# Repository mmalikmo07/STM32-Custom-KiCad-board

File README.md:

# STM32F103 Development Board

A 2-layer, 45 × 40 mm development board built around the STM32F103C8T6 (Arm Cortex-M3, 72 MHz), designed in KiCad 9 from schematic through layout to Gerbers. It's powered and programmed over USB, with SWD for debugging and breakout headers for UART and I²C.

This was my first full board. It began as a guided KiCad tutorial build, which is why the files are named `KiCad-STM32-tut`. Below are the design choices and what I'd change in the next revision.

## Status

**Design complete, not yet fabricated.** The fab-ready Gerbers and drill files are in [`gerbers/`](gerbers/). The next steps are fabrication, assembly and bring-up (see below).

## Block overview

| Block | Implementation | Notes |
|---|---|---|
| MCU | STM32F103C8T6, LQFP-48 | 64 KB flash, 20 KB SRAM |
| Power | USB VBUS (5 V) → AMS1117-3.3 LDO (SOT-223) | 22 µF bulk capacitors on the input and output, as the AMS1117 needs for stability |
| Decoupling | 100 nF on the VDD pins, plus 10 µF bulk on 3.3 V | |
| Analogue supply | VDDA fed from 3.3 V through a 120 Ω ferrite bead, with 1 µF + 10 nF | Keeps digital switching noise off the ADC reference |
| Clock | 16 MHz crystal (3.2 × 2.5 mm), 10 pF load caps | The PLL gives 72 MHz SYSCLK, and the 48 MHz USB clock is derived from it |
| USB | Micro-B (Würth 629105150521), USB FS on PA11/PA12 | 1.5 kΩ pull-up on D+, which the F103 needs because it has no internal one |
| Boot | SPDT slide switch → 10 kΩ → BOOT0 | Selects the system bootloader or flash at reset |
| Debug / IO | 4-pin headers: SWD (SWDIO, SWCLK), USART1 (remapped to PB6/PB7), I²C2 (PB10/PB11, 1.5 kΩ pull-ups) | |
| Indicator | Power LED (0603) | |
| Mechanical | 4 × M2 mounting holes | |

**Layout:** 2 layers, with a solid GND pour on the bottom layer as the return plane. The top layer carries GND, 3.3 V and VBUS pours around the signal routing. Passives are mostly 0402.

## Rev B: what I'd change

These are the issues I found reviewing my own netlist:

1. **USB connector shield is floating.** The shield pads are unconnected. Tying them to GND through a ferrite bead or an RC network (e.g. 1 MΩ ∥ 4.7 nF) would improve EMI and ESD behaviour.
2. **No ESD protection on the USB lines.** Add a TVS array such as the USBLC6-2SC6 on D+/D− and VBUS.
3. **No input protection.** Add a polyfuse on VBUS and reverse-current protection if the board will ever be powered from the headers.
4. **Regulator choice.** An LDO is fine at this board's load. At around 100 mA it dissipates (5 − 3.3) × 0.1 ≈ 0.17 W. If I add peripherals that draw hundreds of mA, I'd move to a buck converter for efficiency.
5. **Connector.** USB-C with 5.1 kΩ CC pull-downs would make it work with modern cables and chargers.

## Bring-up plan

1. Visual inspection, then check continuity and look for shorts between 3.3 V, VBUS and GND
2. Power from a current-limited bench supply and check the 3.3 V rail and its ripple
3. Connect over SWD with an ST-Link and read the device ID
4. Flash a blinky over SWD, then test USB DFU through the BOOT0 switch
5. Check the 16 MHz HSE on a scope, then confirm the PLL by toggling a GPIO with MCO

## Files

```
KiCad-STM32-tut.kicad_pro / .kicad_sch / .kicad_pcb   KiCad 9 project
gerbers/                                             Gerbers, drill files, and a zipped fab package
3d-models/                                           STEP model for the USB connector
```

Tools: KiCad 9, STM32CubeMX (pin planning).

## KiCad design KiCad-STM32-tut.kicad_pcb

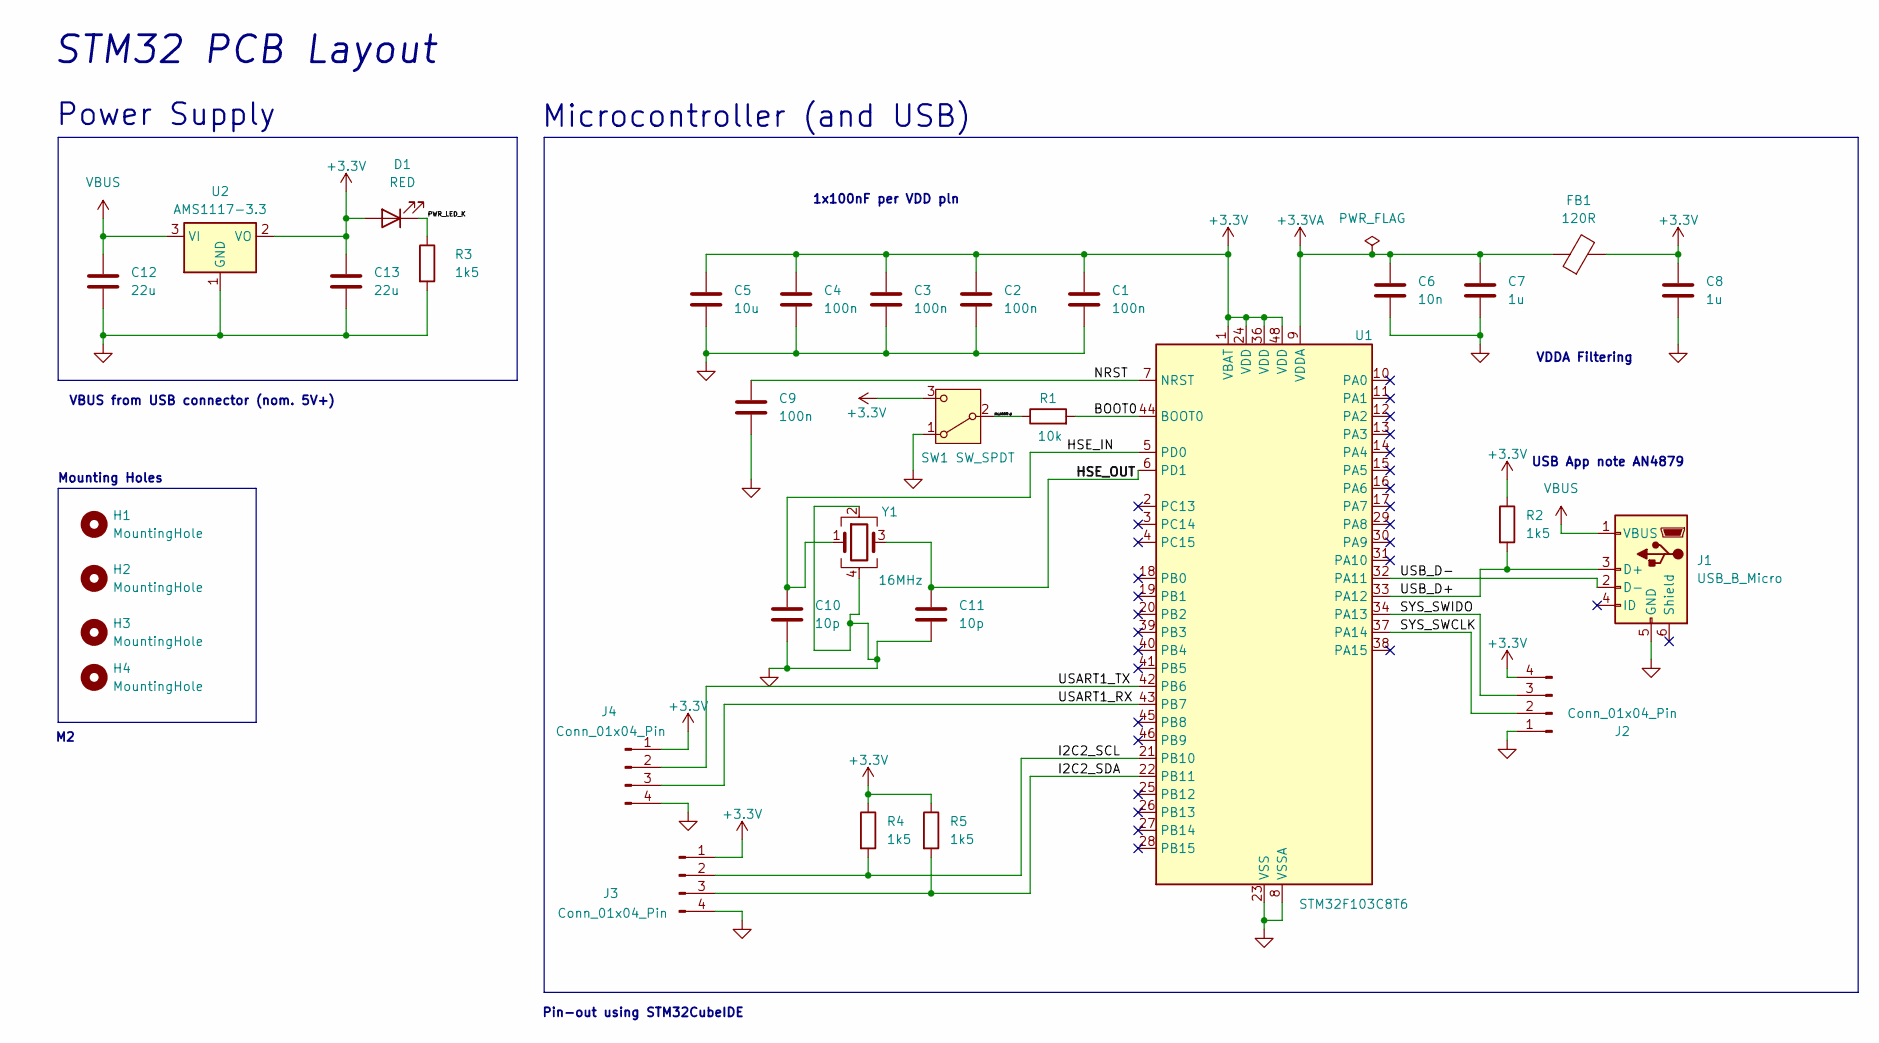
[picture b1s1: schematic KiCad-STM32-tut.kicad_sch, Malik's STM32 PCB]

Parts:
C1, C2, C3, C4, C9: 100n; C_0402_1005Metric
C5: 10u; C_0402_1005Metric
C6: 10n; C_0402_1005Metric
C7, C8: 1u; C_0402_1005Metric
C10, C11: 10p; C_0402_1005Metric
C12, C13: 22u; C_0805_2012Metric
D1: RED; LED_0603_1608Metric
FB1: 120R; L_0603_1608Metric
H1, H2, H3, H4: MountingHole; MountingHole_2.2mm_M2
J1: USB_B_Micro; USB_Micro-B_Wuerth_629105150521
J2, J3, J4: Conn_01x04_Pin; PinHeader_1x04_P2.54mm_Vertical
R1: 10k; R_0402_1005Metric
R2, R3, R4, R5: 1k5; R_0402_1005Metric
SW1: SW_SPDT; SW_SPDT_PCM12
U1: STM32F103C8T6; LQFP-48_7x7mm_P0.5mm
U2: AMS1117-3.3; SOT-223-3_TabPin2
Y1: 16MHz; Crystal_SMD_3225-4Pin_3.2x2.5mm

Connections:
+3.3V: C1.1, C2.1, C3.1, C4.1, C5.1, C8.1, C13.1, D1.2 (A), FB1.2, J2.4, J3.1, J4.1, R2.1, R4.1, R5.1, SW1.3 (C), U1.1 (VBAT), U1.24 (VDD), U1.36 (VDD), U1.48 (VDD), U2.2 (VO)
+3.3VA: C6.1, C7.1, FB1.1, U1.9 (VDDA)
/BOOT0: R1.2, U1.44 (BOOT0)
/HSE_IN: C10.1, U1.5 (PD0), Y1.1
/HSE_OUT: C11.1, U1.6 (PD1), Y1.3
/I2C2_SCL: J3.2, R4.2, U1.21 (PB10)
/I2C2_SDA: J3.3, R5.2, U1.22 (PB11)
/NRST: C9.1, U1.7 (NRST)
/PWR_LED_K: D1.1 (K), R3.1
/SW_BOOT0 :): R1.1, SW1.2 (B)
/SYS_SWCLK: J2.2, U1.37 (PA14)
/SYS_SWIDO: J2.3, U1.34 (PA13)
/USART1_RX: J4.3, U1.43 (PB7)
/USART1_TX: J4.2, U1.42 (PB6)
/USB_D+: J1.3 (D+), R2.2, U1.33 (PA12)
/USB_D-: J1.2 (D-), U1.32 (PA11)
GND: C1.2, C2.2, C3.2, C4.2, C5.2, C6.2, C7.2, C8.2, C9.2, C10.2, C11.2, C12.2, C13.2, J1.5 (GND), J2.1, J3.4, J4.4, R3.2, SW1.1 (A), U1.8 (VSSA), U1.23 (VSS), U1.35 (VSS), U1.47 (VSS), U2.1 (GND), Y1.2, Y1.4
VBUS: C12.1, J1.1 (VBUS), U2.3 (VI)

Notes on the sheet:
Pin-out using STM32CubeIDE
Power Supply
USB App note AN4879
VDDA Filtering
STM32 PCB Layout
Microcontroller (and USB)
1x100nF per VDD pln
Mounting Holes
VBUS from USB connector (nom. 5V+)

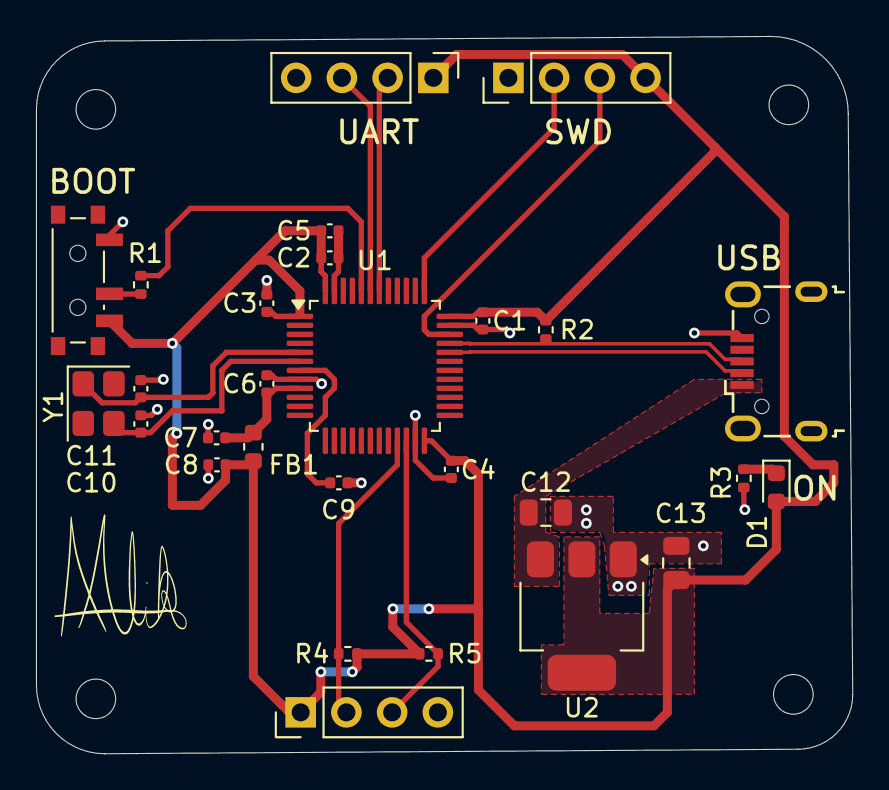
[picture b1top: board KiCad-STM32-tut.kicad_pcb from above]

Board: 2 copper layers, 45.4 x 39.8 mm, 32 parts (0 on the bottom side), 18 nets.

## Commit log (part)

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2026-06-26 Initial commit - STM32 PCB design
2026-06-26 pcbREADME.md
2026-06-26 Updated_PCB_README.md
